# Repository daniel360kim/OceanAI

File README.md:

<!-- Project Logo -->
<div align="center">

  <h1 align="center">OceanAI</h1>
  
  <p align="center">
    A robotic and software orientated ocean development.
    <br />
    <a href="https://www.youtube.com/watch?v=8TJVxcPY-2g&t=32s&ab_channel=NMRocketry"><strong>See the video »</strong></a>
    <br />
    <br />
  </p>
</div>

<br>
  <h2>Table of Contents</h2>
  <ol>
    <li>
      <a href="#about-the-project">About The Project</a>
    </li>
    <li>
      <a href="#getting-started">Getting Started</a>
      <ul>
        <li><a href="#AUV Software">AUV Software</a></li>
        <li><a href="#Graphical User Interface">Graphical User Interface</a></li>
      </ul>
    </li>
    <li><a href="#license">License</a></li>
    <li><a href="#contact">Contact</a></li>
  </ol>

# About the Project
This project aims at creating an autonomous underwater vehicle (AUV) that utilizes cameras, sensors, a microcontroller, and GPS to categorize, identify, and map underwater trash. Detection of litter will be performed with a deep learning model - optimized to run on a microcontroller - allowing for cheap and power-efficient inference of underwater footage.

Main components of the project include:
* [AUV Control Board](https://github.com/daniel360kim/OceanAI/tree/master/PCBs)
* [AUV Software](https://github.com/daniel360kim/OceanAI/tree/master/software/sub_driver)
* [AUV CAD Model](https://github.com/daniel360kim/OceanAI/tree/master/CAD)
* [Deep Learning Model](https://github.com/daniel360kim/OceanAI/tree/master/software/detection_model)

# Getting Started
## AUV Software
[VSCode](https://code.visualstudio.com/) and
[PlatformIO](https://platformio.org/) are used to build and upload the software to the AUV.
1. Install VSCode and the PlatformIO extension.
2. Clone the repository.
```sh
git clone https://github.com/daniel360kim/OceanAI.git
```
3. Go to PlatformIO home and go to the 'Projects' tab.
4. Click 'Add Existing Project' and select the `software/sub_driver` folder.
5. Make sure you have the Teensy 4.1 core installed.
6. Connect the AUV through USB and click the 'Upload' button.
<br></br>

## Graphical User Interface

<br></br>
The GUI is built using [ElectricUI](https://electricui.com/). ElectricUI requires:
* [Node.js](https://nodejs.org/en/)
* [Yarn](https://yarnpkg.com/)

1. Install Node.js, [available from their website](https://nodejs.org/en/).
2. Install Yarn.
```sh
npm install -g yarn
```
3. Install ElectricUI, [available here](https://registry.eui.io/arc/latest/arc_latest_windows_amd64.msi)
4. Check everything installed and can be found in your PATH
```sh
arc info
```
5. Clone the repository if you haven't already.
```sh
git clone https://github.com/daniel360kim/OceanAI.git
```
6. Open the GUI project with ElectricUI. `software/auv_gui`
7. Run the GUI.
```sh
arc start
```

# License
Distributed under the MIT License. See `LICENSE` for more information.

# Contact
* Daniel Kim - nmrs.thrust@gmail.com - [YouTube](https://www.youtube.com/channel/UC0VazqJrUQiJGd_Tedn47zA) - Instagram: @us_rockets
* Project Link: https://github.com/daniel360kim/OceanAI

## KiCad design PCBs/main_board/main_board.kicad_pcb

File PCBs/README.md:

# PCBs
## Contains all the files for the printed circuit boards.

### main_board
* The PCB on the submarine that controls the submarine.
* This is the main board that controls navigation, outputs, loggins etc.

### transmitter_board
* This is an optional module that is floating in the water.
* It is connnected through a cable to the main board.
* It is above water so it can access GPS, RF, and other radio frequencies.

### sensor_board
* This board is at the front of the submarine. 
* It reads the underwater sensors and sends the data to the main board through I2C.
* It is not self powered - must have a clean 3.3V power supply.
* Programmed through SWD.

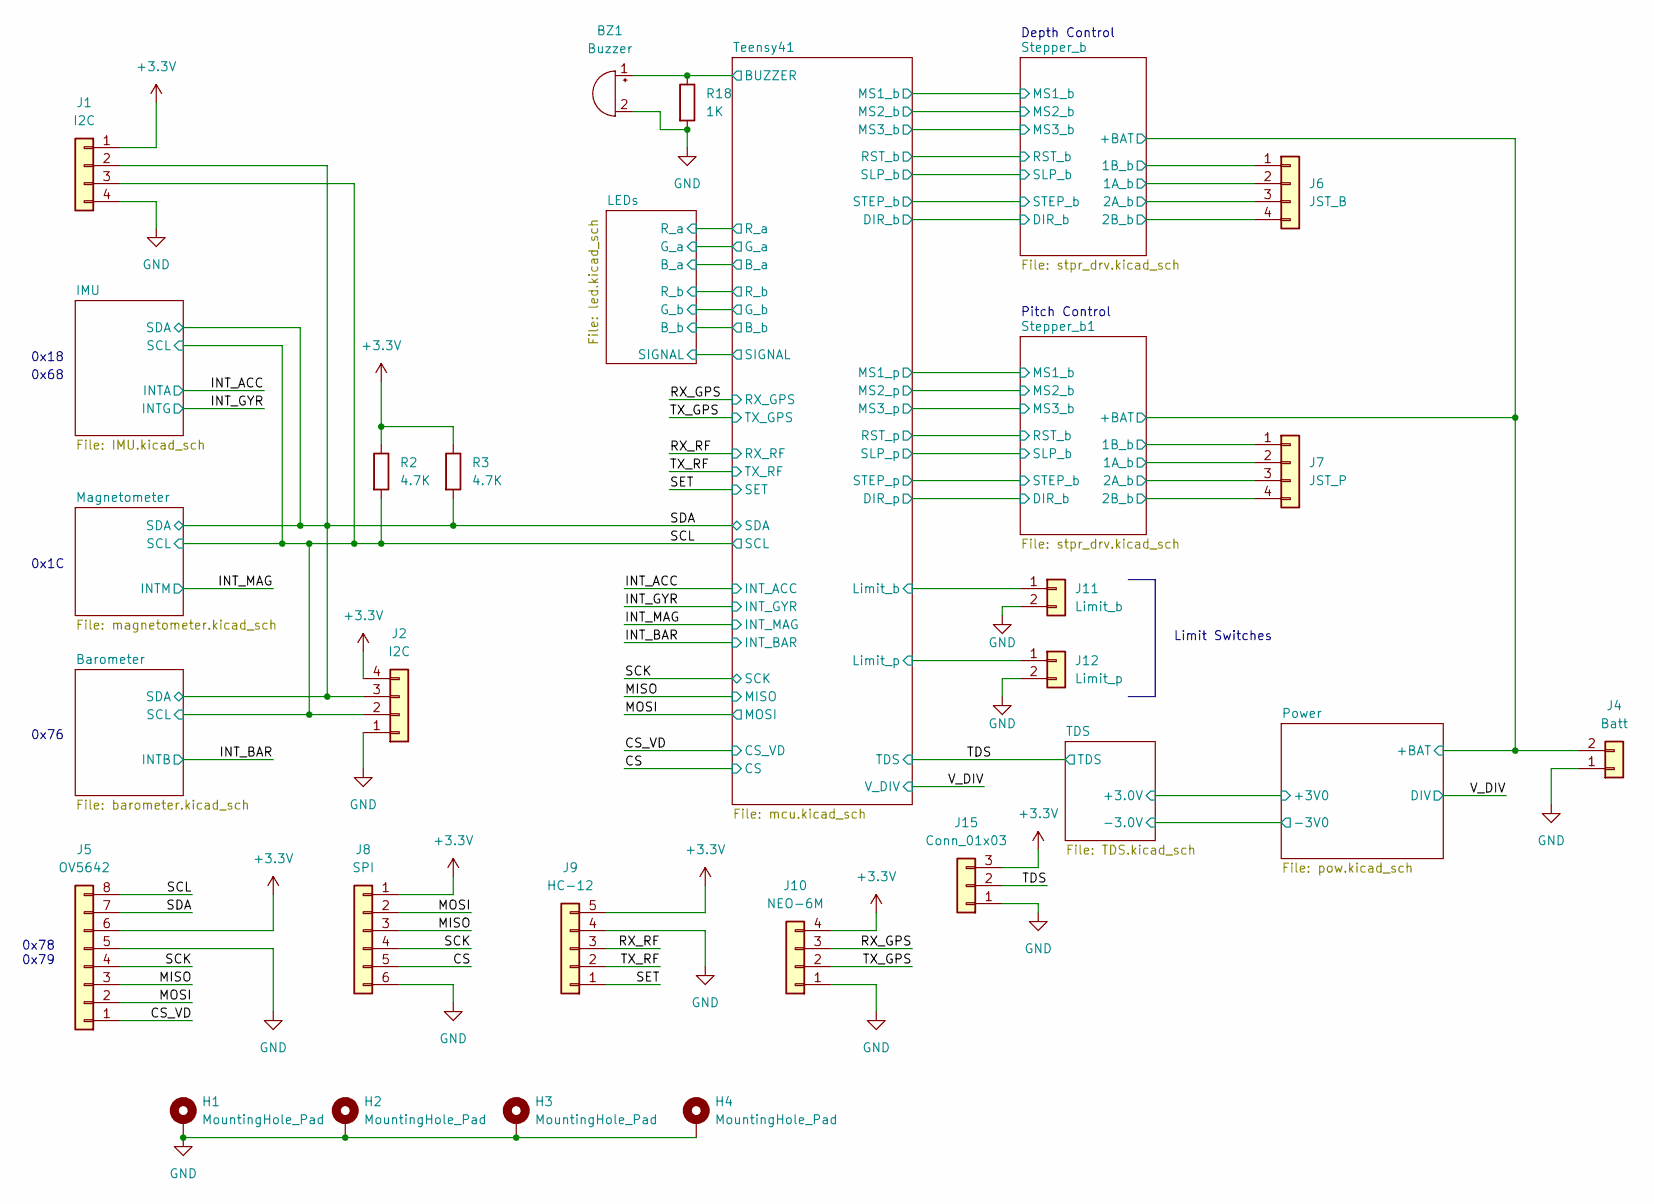
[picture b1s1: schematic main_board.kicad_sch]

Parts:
BZ1: Buzzer; Buzzer_Murata_PKMCS0909E
H1, H2, H3, H4: MountingHole_Pad; MountingHole_3mm_Pad
J1: I2C; JST_EH_B4B-EH-A_1x04_P2.50mm_Vertical
J2: I2C; PinHeader_1x04_P2.54mm_Vertical
J4: Batt; TerminalBlock_MetzConnect_Type101_RT01602HBWC_1x02_P5.08mm_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
J5: OV5642; JST_EH_B8B-EH-A_1x08_P2.50mm_Vertical
J6: JST_B; JST_EH_B4B-EH-A_1x04_P2.50mm_Vertical
J7: JST_P; JST_EH_B4B-EH-A_1x04_P2.50mm_Vertical
J8: SPI; PinHeader_1x06_P2.54mm_Vertical
J9: HC-12; JST_EH_B5B-EH-A_1x05_P2.50mm_Vertical
J10: NEO-6M; JST_EH_B4B-EH-A_1x04_P2.50mm_Vertical
J11: Limit_b; JST_EH_B2B-EH-A_1x02_P2.50mm_Vertical
J12: Limit_p; JST_EH_B2B-EH-A_1x02_P2.50mm_Vertical
J15: Conn_01x03; PinHeader_1x03_P2.54mm_Vertical
R2, R3: 4.7K; R_0603_1608Metric
R18: 1K; R_0603_1608Metric

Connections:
+3V3: J1.1, J2.4, J5.6, J8.1, J9.5, J10.4, J15.3, R2.1, R3.1; also elsewhere on the board
/CS: J8.5; also elsewhere on the board
/CS_VD: J5.1; also elsewhere on the board
/MISO: J5.3, J8.3; also elsewhere on the board
/MOSI: J5.2, J8.2; also elsewhere on the board
/RX_GPS: J10.3; also elsewhere on the board
/RX_RF: J9.3; also elsewhere on the board
/SCK: J5.4, J8.4; also elsewhere on the board
/SCL: J1.3, J2.2, J5.8, R2.2; also elsewhere on the board
/SDA: J1.2, J2.3, J5.7, R3.2; also elsewhere on the board
/SET: J9.1; also elsewhere on the board
/Stepper_b1/1A_b: J7.2; also elsewhere on the board
/Stepper_b1/1B_b: J7.1; also elsewhere on the board
/Stepper_b1/2A_b: J7.3; also elsewhere on the board
/Stepper_b1/2B_b: J7.4; also elsewhere on the board
/Stepper_b/1A_b: J6.2; also elsewhere on the board
/Stepper_b/1B_b: J6.1; also elsewhere on the board
/Stepper_b/2A_b: J6.3; also elsewhere on the board
/Stepper_b/2B_b: J6.4; also elsewhere on the board
/Stepper_b/VMM: J4.2; also elsewhere on the board
/TDS: J15.2; also elsewhere on the board
/TX_GPS: J10.2; also elsewhere on the board
/TX_RF: J9.2; also elsewhere on the board
/Teensy41/BUZZER: BZ1.1 (-), R18.1; also elsewhere on the board
/Teensy41/Limit_b: J11.1; also elsewhere on the board
/Teensy41/Limit_p: J12.1; also elsewhere on the board
GND: BZ1.2 (+), H1.1, H2.1, H3.1, H4.1, J1.4, J2.1, J4.1, J5.5, J8.6, J9.4, J10.1, J11.2, J12.2, J15.1, R18.2; also elsewhere on the board

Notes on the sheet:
Depth Control
0x1C
0x68
0x76
0x18
Pitch Control
Limit Switches
0x78 0x79

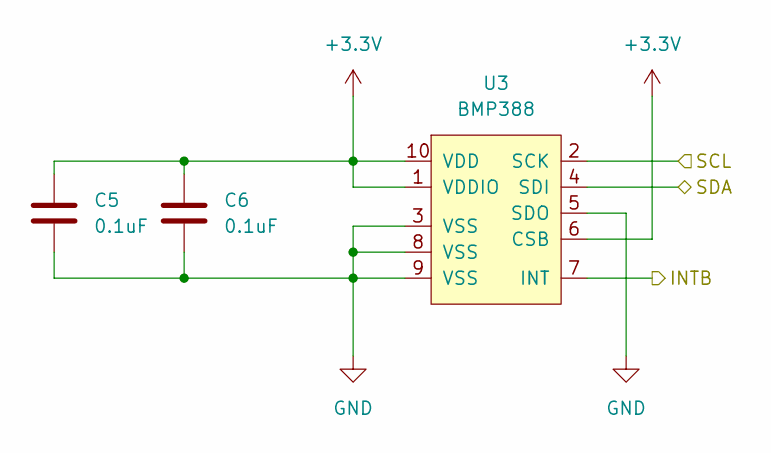
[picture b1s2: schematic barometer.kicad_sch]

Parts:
C5, C6: 0.1uF; C_0603_1608Metric
U3: BMP388; PQFN50P200X200X80-10N

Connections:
+3V3: C5.1, C6.1, U3.1 (VDDIO), U3.6 (CSB), U3.10 (VDD); also elsewhere on the board
/INT_BAR: U3.7 (INT); also elsewhere on the board
/SCL: U3.2 (SCK); also elsewhere on the board
/SDA: U3.4 (SDI); also elsewhere on the board
GND: C5.2, C6.2, U3.3 (VSS), U3.5 (SDO), U3.8 (VSS), U3.9 (VSS); also elsewhere on the board

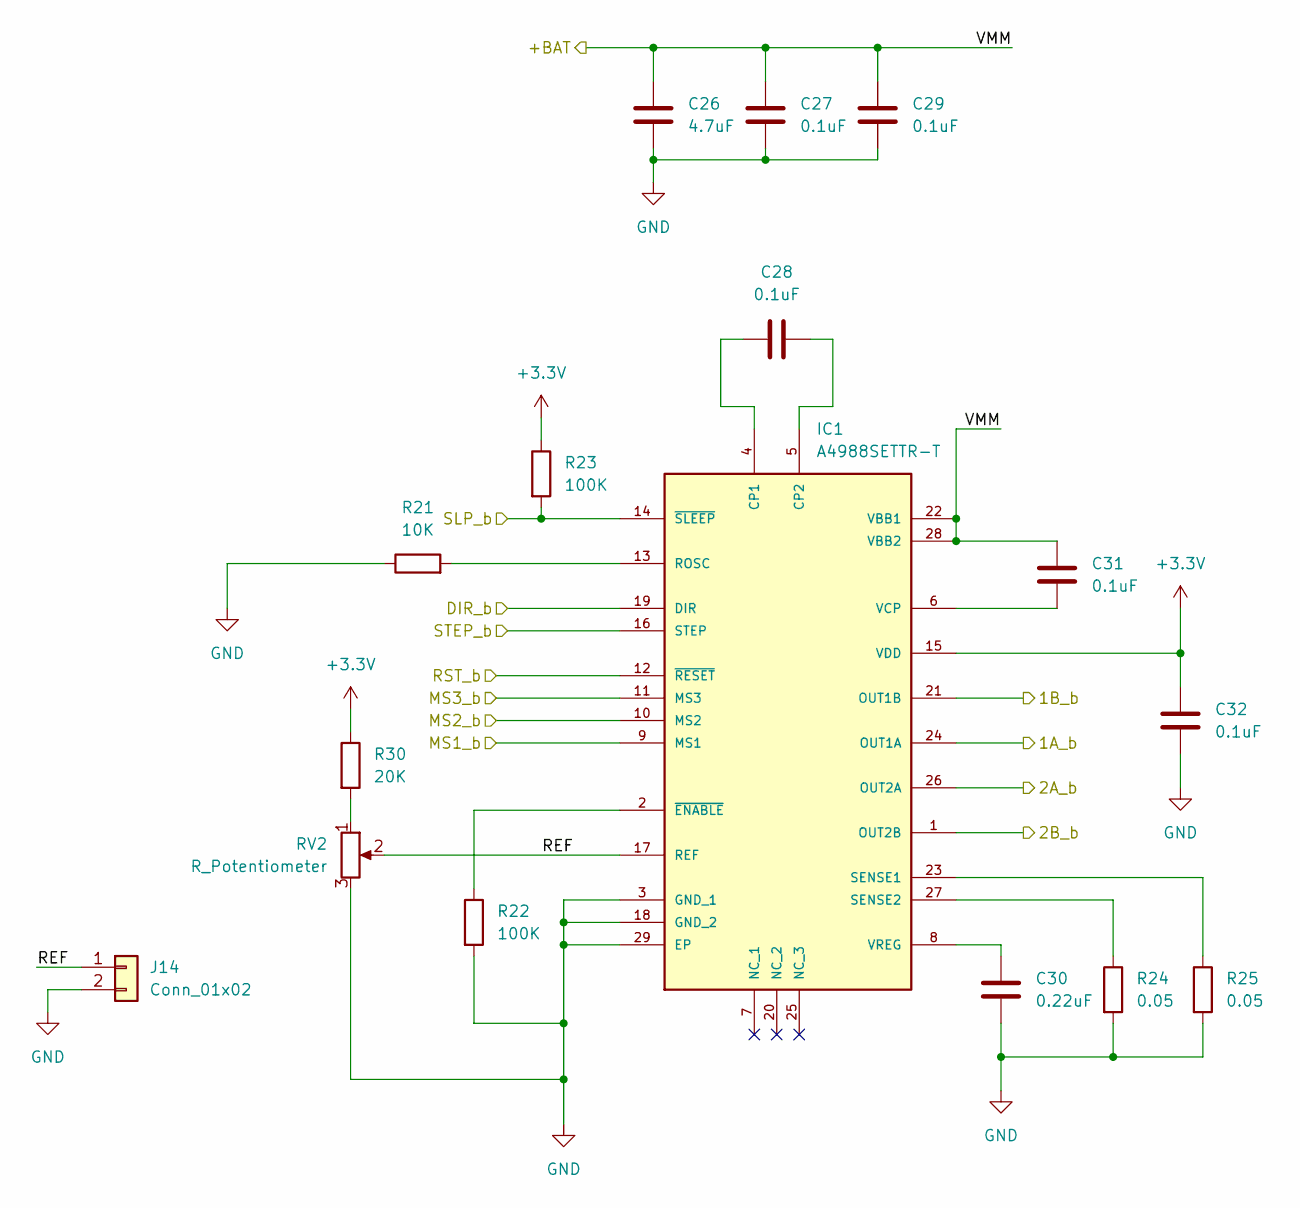
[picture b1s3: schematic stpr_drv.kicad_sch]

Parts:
C26: 4.7uF; C_0603_1608Metric
C27, C28, C29, C31, C32: 0.1uF; C_0603_1608Metric
C30: 0.22uF; C_0603_1608Metric
IC1: A4988SETTR-T; QFN50P500X500X100-29N; MANUFACTURER_PART_NUMBER A4988SETTR-T
J14: Conn_01x02; PinHeader_1x02_P2.54mm_Vertical
R21: 10K; R_0603_1608Metric
R22, R23: 100K; R_0603_1608Metric
R24, R25: 0.05; R_0603_1608Metric
R30: 20K; R_0603_1608Metric
RV2: R_Potentiometer; TRIM_35WR10KLFTR

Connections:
+3V3: C32.1, IC1.15 (VDD), R23.1, R30.1; also elsewhere on the board
/Stepper_b/1A_b: IC1.24 (OUT1A); also elsewhere on the board
/Stepper_b/1B_b: IC1.21 (OUT1B); also elsewhere on the board
/Stepper_b/2A_b: IC1.26 (OUT2A); also elsewhere on the board
/Stepper_b/2B_b: IC1.1 (OUT2B); also elsewhere on the board
/Stepper_b/DIR_b: IC1.19 (DIR); also elsewhere on the board
/Stepper_b/MS1_b: IC1.9 (MS1); also elsewhere on the board
/Stepper_b/MS2_b: IC1.10 (MS2); also elsewhere on the board
/Stepper_b/MS3_b: IC1.11 (MS3); also elsewhere on the board
/Stepper_b/REF: IC1.17 (REF), J14.1, RV2.2
/Stepper_b/RST_b: IC1.12 (~RESET); also elsewhere on the board
/Stepper_b/SLP_b: IC1.14 (~SLEEP), R23.2; also elsewhere on the board
/Stepper_b/STEP_b: IC1.16 (STEP); also elsewhere on the board
/Stepper_b/VMM: C26.1, C27.1, C29.1, C31.1, IC1.22 (VBB1), IC1.28 (VBB2); also elsewhere on the board
GND: C26.2, C27.2, C29.2, C30.2, C32.2, IC1.3 (GND_1), IC1.18 (GND_2), IC1.29 (EP), J14.2, R21.1, R22.2, R24.2, R25.2, RV2.3; also elsewhere on the board
unnamed: C28.1, IC1.4 (CP1)
unnamed: C28.2, IC1.5 (CP2)
unnamed: C30.1, IC1.8 (VREG)
unnamed: C31.2, IC1.6 (VCP)
unnamed: IC1.2 (~ENABLE), R22.1
unnamed: IC1.13 (ROSC), R21.2
unnamed: IC1.23 (SENSE1), R25.1
unnamed: IC1.27 (SENSE2), R24.1
unnamed: R30.2, RV2.1

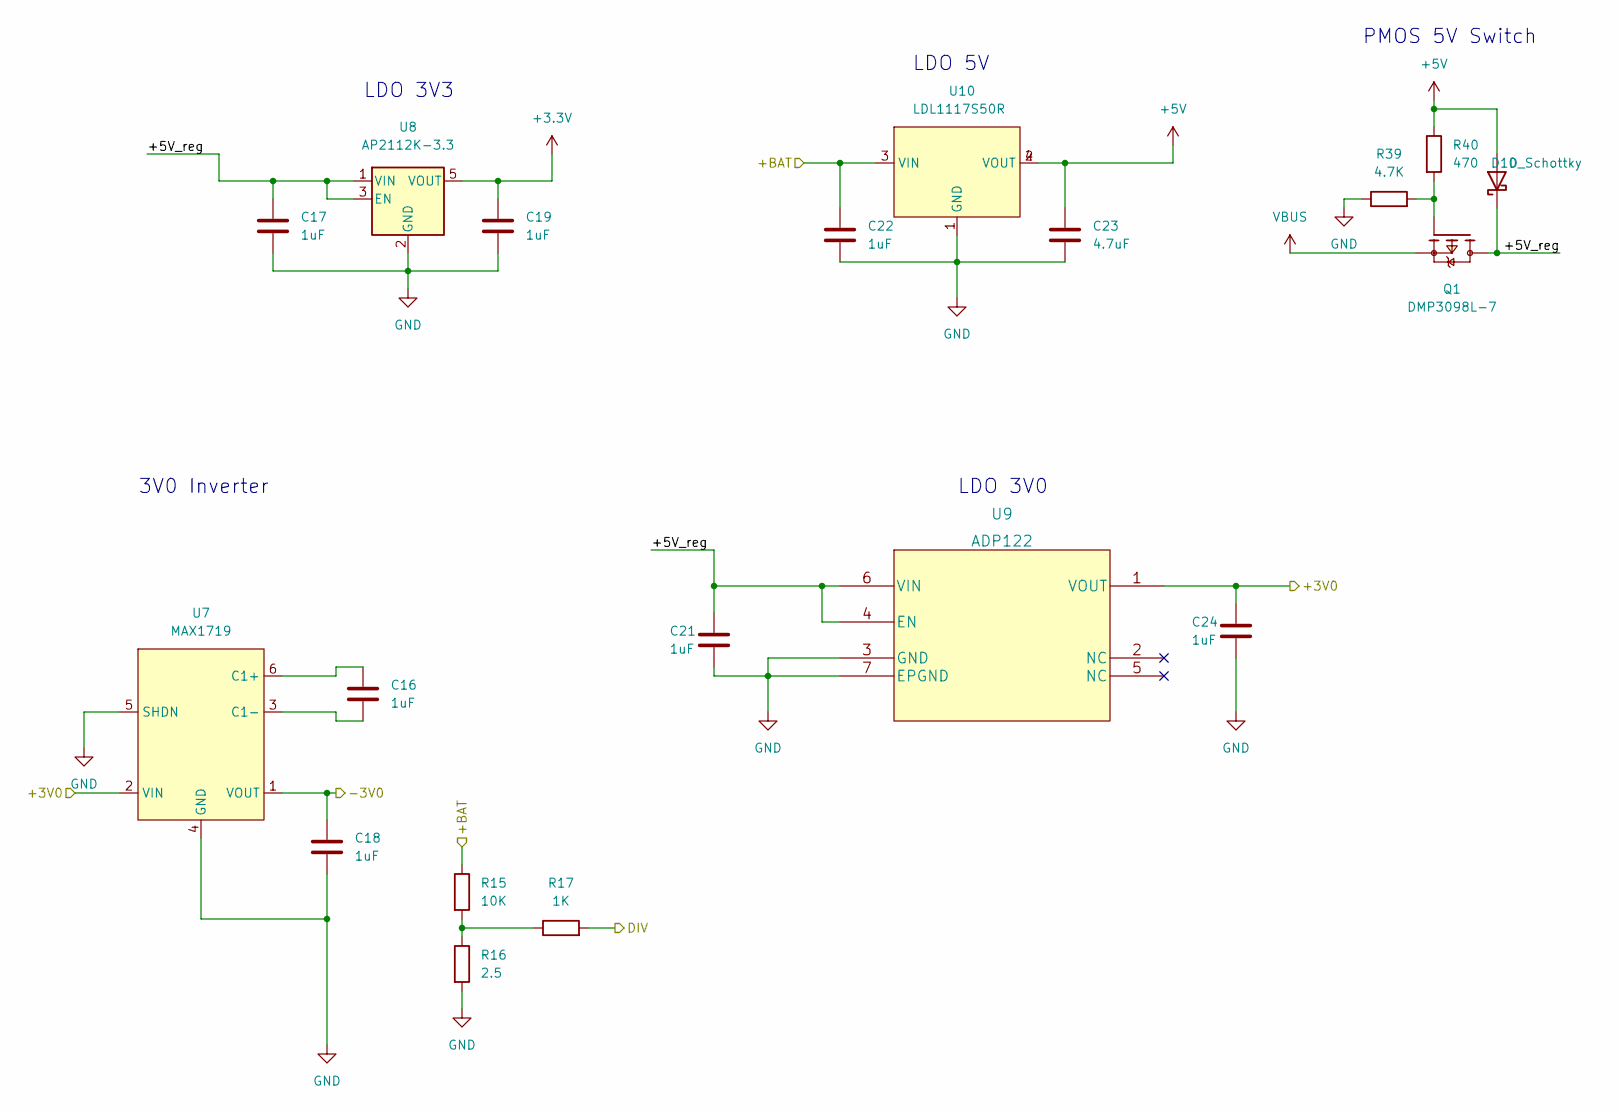
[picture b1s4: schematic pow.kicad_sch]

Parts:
C16, C17, C18, C19, C21, C22, C24: 1uF; C_0603_1608Metric
C23: 4.7uF; C_0603_1608Metric
D10: D_Schottky; DIOM4427X270N
Q1: DMP3098L-7; SOT91P240X110-3N; PARTREV 8 - 2
R15: 10K; R_0603_1608Metric
R16: 2.5; R_0603_1608Metric
R17: 1K; R_0603_1608Metric
R39: 4.7K; R_0603_1608Metric
R40: 470; R_0603_1608Metric
U7: MAX1719; SOT95P280X145-6N
U8: AP2112K-3.3; SOT95P285X140-5N
U9: ADP122; SON65P200X200X65-7N
U10: LDL1117S50R; SOT230P700X180-4N

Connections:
+3V3: C19.1, U8.5 (VOUT); also elsewhere on the board
+5V: C23.1, D10.A, R40.1, U10.2 (VOUT), U10.4 (VOUT); also elsewhere on the board
/Power/+3V0: C24.1, U7.2 (VIN), U9.1 (VOUT); also elsewhere on the board
/Power/+5V_reg: C17.1, C21.1, D10.C (K), Q1.3, U8.1 (VIN), U8.3 (EN), U9.4 (EN), U9.6 (VIN)
/Stepper_b/VMM: C22.1, R15.1, U10.3 (VIN); also elsewhere on the board
/TDS/RST: C18.1, U7.1 (VOUT); also elsewhere on the board
/V_DIV: R17.2; also elsewhere on the board
GND: C17.2, C18.2, C19.2, C21.2, C22.2, C23.2, C24.2, R16.2, R39.1, U7.4 (GND), U7.5 (SHDN), U8.2 (GND), U9.3 (GND), U9.7 (EPGND), U10.1 (GND); also elsewhere on the board
unnamed: C16.1, U7.6 (C1+)
unnamed: C16.2, U7.3 (C1-)
unnamed: Q1.1, R39.2, R40.2
unnamed: R15.2, R16.1, R17.1
VBUS: Q1.2; also elsewhere on the board

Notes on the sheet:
PMOS 5V Switch
LDO 5V
3V0 Inverter
LDO 3V3
LDO 3V0

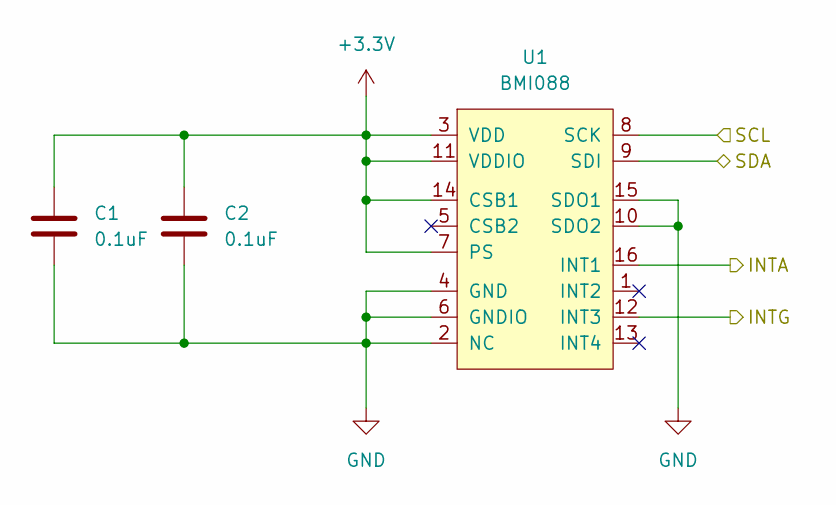
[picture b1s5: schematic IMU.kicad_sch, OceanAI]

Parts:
C1, C2: 0.1uF; C_0603_1608Metric
U1: BMI088; PQFN50P450X300X100-16N

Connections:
+3V3: C1.1, C2.1, U1.3 (VDD), U1.7 (PS), U1.11 (VDDIO), U1.14 (CSB1); also elsewhere on the board
/INT_ACC: U1.16 (INT1); also elsewhere on the board
/INT_GYR: U1.12 (INT3); also elsewhere on the board
/SCL: U1.8 (SCK); also elsewhere on the board
/SDA: U1.9 (SDI); also elsewhere on the board
GND: C1.2, C2.2, U1.2 (NC), U1.4 (GND), U1.6 (GNDIO), U1.10 (SDO2), U1.15 (SDO1); also elsewhere on the board

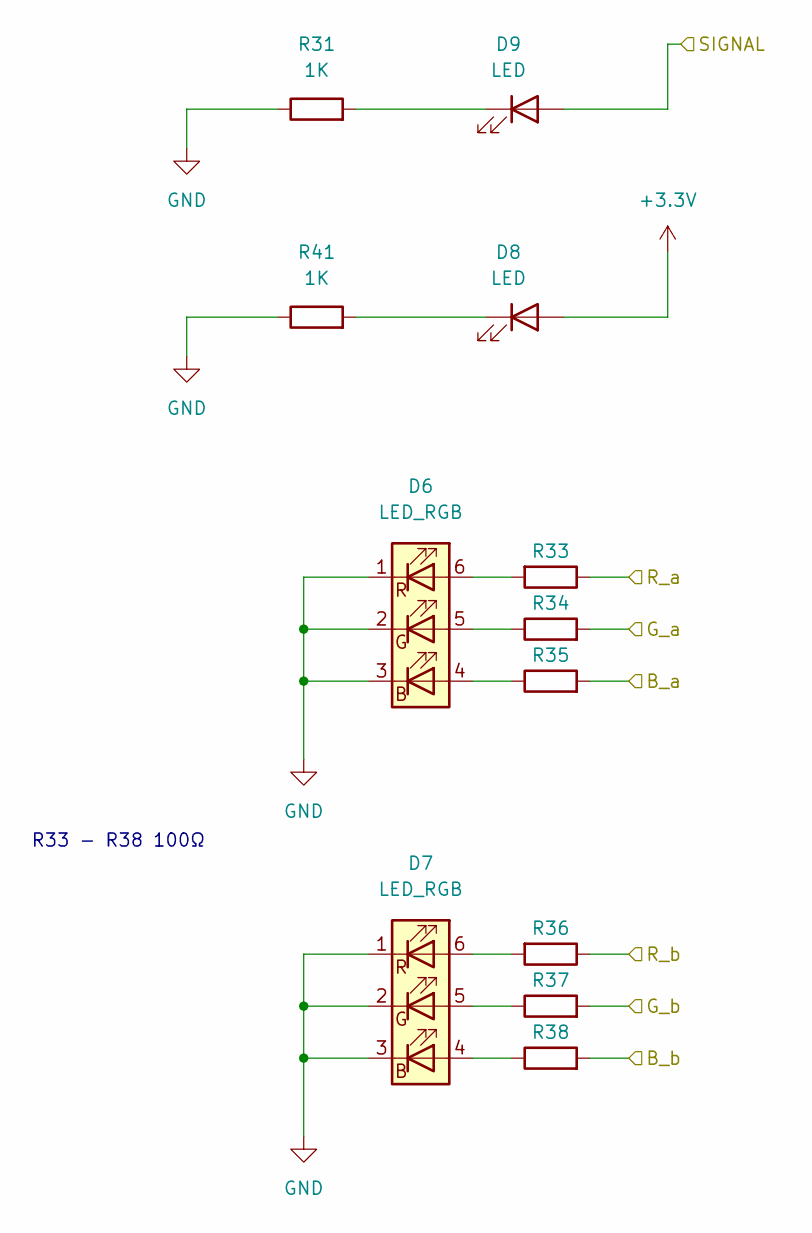
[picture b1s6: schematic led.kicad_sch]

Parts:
D6, D7: LED_RGB; LED_RGB_5050-6
D8, D9: LED; LED_0603_1608Metric
R31, R41: 1K; R_0603_1608Metric
R33, R35, R36, R38: R; R_0603_1608Metric
R34, R37: R_0603_1608Metric

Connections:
+3V3: D8.2 (A); also elsewhere on the board
/LEDs/B_a: R35.2; also elsewhere on the board
/LEDs/B_b: R38.2; also elsewhere on the board
/LEDs/G_a: R34.2; also elsewhere on the board
/LEDs/G_b: R37.2; also elsewhere on the board
/LEDs/R_a: R33.1; also elsewhere on the board
/LEDs/R_b: R36.1; also elsewhere on the board
/LEDs/SIGNAL: D9.2 (A); also elsewhere on the board
GND: D6.1 (RK), D6.2 (GK), D6.3 (BK), D7.1 (RK), D7.2 (GK), D7.3 (BK), R31.1, R41.1; also elsewhere on the board
unnamed: D6.4 (BA), R35.1
unnamed: D6.5 (GA), R34.1
unnamed: D6.6 (RA), R33.2
unnamed: D7.4 (BA), R38.1
unnamed: D7.5 (GA), R37.1
unnamed: D7.6 (RA), R36.2
unnamed: D8.1 (K), R41.2
unnamed: D9.1 (K), R31.2

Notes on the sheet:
R33 - R38 100Ω

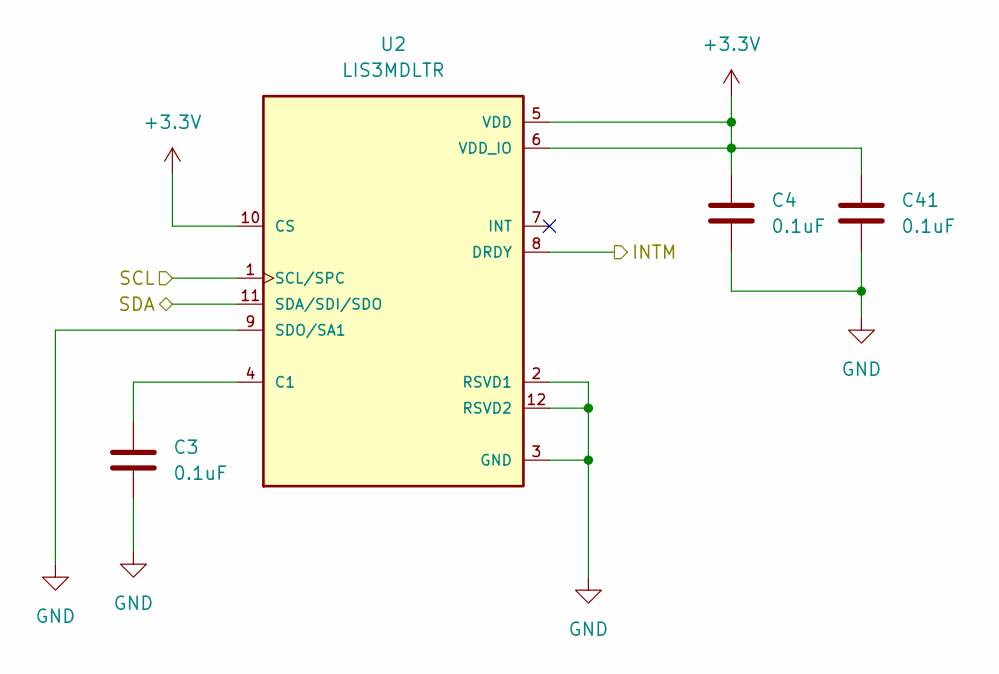
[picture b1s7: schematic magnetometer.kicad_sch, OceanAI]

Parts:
C3, C4, C41: 0.1uF; C_0603_1608Metric
U2: LIS3MDLTR; XDCR_LIS3MDLTR; PARTREV 6

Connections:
+3V3: C4.1, C41.1, U2.5 (VDD), U2.6 (VDD_IO), U2.10 (CS); also elsewhere on the board
/INT_MAG: U2.8 (DRDY); also elsewhere on the board
/SCL: U2.1 (SCL/SPC); also elsewhere on the board
/SDA: U2.11 (SDA/SDI/SDO); also elsewhere on the board
GND: C3.2, C4.2, C41.2, U2.2 (RSVD1), U2.3 (GND), U2.9 (SDO/SA1), U2.12 (RSVD2); also elsewhere on the board
unnamed: C3.1, U2.4 (C1)

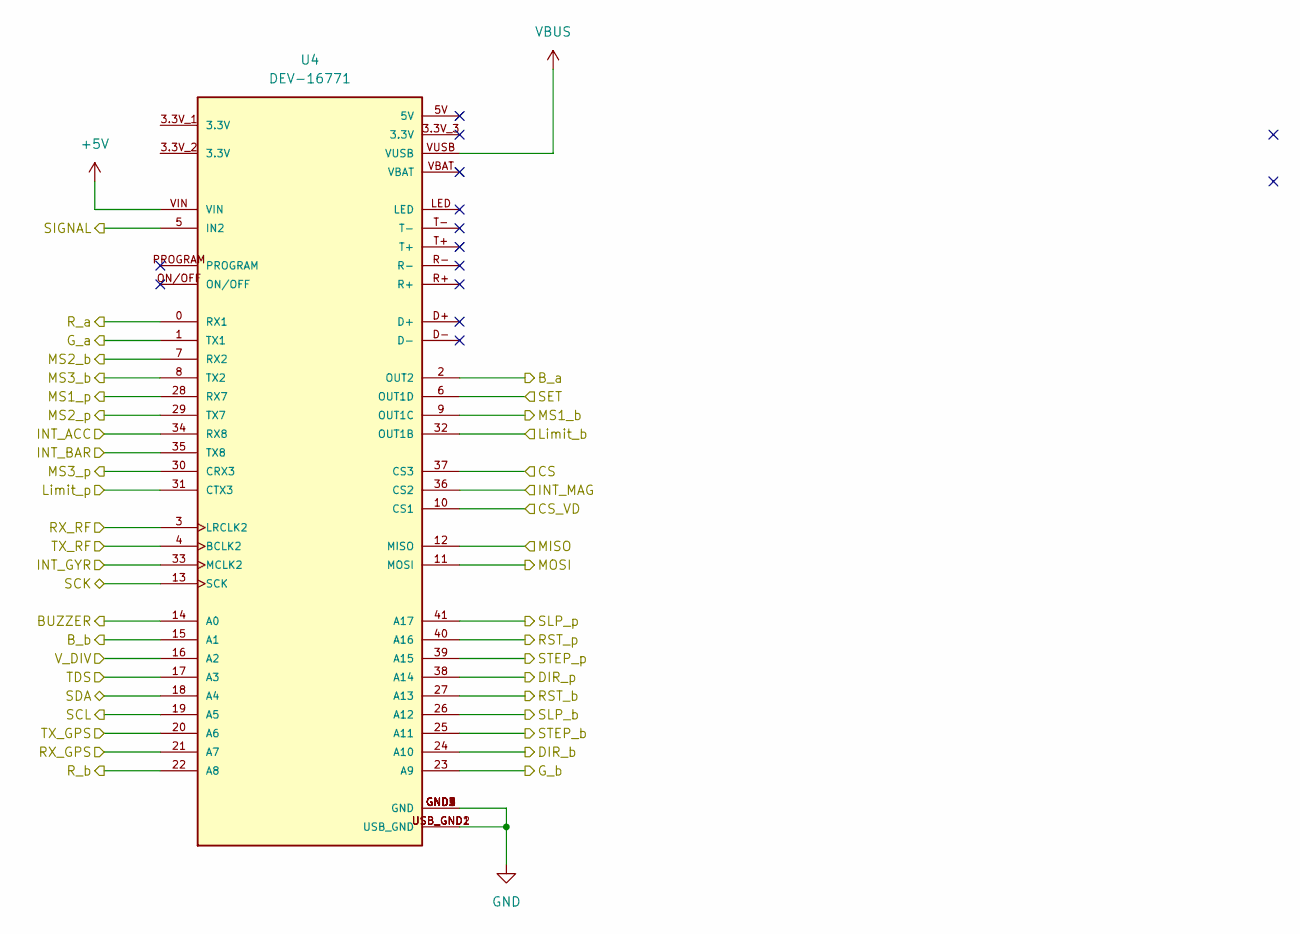
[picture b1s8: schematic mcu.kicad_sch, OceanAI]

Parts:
U4: DEV-16771; MODULE_DEV-16771; PARTREV 4.1

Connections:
+5V: U4.VIN; also elsewhere on the board
/CS: U4.37 (CS3); also elsewhere on the board
/CS_VD: U4.10 (CS1); also elsewhere on the board
/INT_ACC: U4.34 (RX8); also elsewhere on the board
/INT_BAR: U4.35 (TX8); also elsewhere on the board
/INT_GYR: U4.33 (MCLK2); also elsewhere on the board
/INT_MAG: U4.36 (CS2); also elsewhere on the board
/LEDs/B_a: U4.2 (OUT2); also elsewhere on the board
/LEDs/B_b: U4.15 (A1); also elsewhere on the board
/LEDs/G_a: U4.1 (TX1); also elsewhere on the board
/LEDs/G_b: U4.23 (A9); also elsewhere on the board
/LEDs/R_a: U4.0 (RX1); also elsewhere on the board
/LEDs/R_b: U4.22 (A8); also elsewhere on the board
/LEDs/SIGNAL: U4.5 (IN2); also elsewhere on the board
/MISO: U4.12 (MISO); also elsewhere on the board
/MOSI: U4.11 (MOSI); also elsewhere on the board
/RX_GPS: U4.21 (A7); also elsewhere on the board
/RX_RF: U4.3 (LRCLK2); also elsewhere on the board
/SCK: U4.13 (SCK); also elsewhere on the board
/SCL: U4.19 (A5); also elsewhere on the board
/SDA: U4.18 (A4); also elsewhere on the board
/SET: U4.6 (OUT1D); also elsewhere on the board
/Stepper_b1/DIR_b: U4.38 (A14); also elsewhere on the board
/Stepper_b1/MS1_b: U4.28 (RX7); also elsewhere on the board
/Stepper_b1/MS2_b: U4.29 (TX7); also elsewhere on the board
/Stepper_b1/MS3_b: U4.30 (CRX3); also elsewhere on the board
/Stepper_b1/RST_b: U4.40 (A16); also elsewhere on the board
/Stepper_b1/SLP_b: U4.41 (A17); also elsewhere on the board
/Stepper_b1/STEP_b: U4.39 (A15); also elsewhere on the board
/Stepper_b/DIR_b: U4.24 (A10); also elsewhere on the board
/Stepper_b/MS1_b: U4.9 (OUT1C); also elsewhere on the board
/Stepper_b/MS2_b: U4.7 (RX2); also elsewhere on the board
/Stepper_b/MS3_b: U4.8 (TX2); also elsewhere on the board
/Stepper_b/RST_b: U4.27 (A13); also elsewhere on the board
/Stepper_b/SLP_b: U4.26 (A12); also elsewhere on the board
/Stepper_b/STEP_b: U4.25 (A11); also elsewhere on the board
/TDS: U4.17 (A3); also elsewhere on the board
/TX_GPS: U4.20 (A6); also elsewhere on the board
/TX_RF: U4.4 (BCLK2); also elsewhere on the board
/Teensy41/BUZZER: U4.14 (A0); also elsewhere on the board
/Teensy41/Limit_b: U4.32 (OUT1B); also elsewhere on the board
/Teensy41/Limit_p: U4.31 (CTX3); also elsewhere on the board
/V_DIV: U4.16 (A2); also elsewhere on the board
GND: U4.GND1 (GND), U4.GND2 (GND), U4.GND3 (GND), U4.GND4 (GND), U4.GND5 (GND), U4.USB_GND1 (USB_GND), U4.USB_GND2 (USB_GND); also elsewhere on the board
VBUS: U4.VUSB; also elsewhere on the board

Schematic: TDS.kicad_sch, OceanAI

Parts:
C7: 1nF; C_0603_1608Metric
C8, C9, C14, C15: 0.1uF; C_0603_1608Metric
C10, C13: 1uF; C_0603_1608Metric
C11, C12: 4.7uF; C_0603_1608Metric
D1, D2, D3, D4, D5: 1N4148WS; D_SOD-323
J3: PROBE; TerminalBlock_MetzConnect_Type101_RT01602HBWC_1x02_P5.08mm_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
R1: 1M; R_0603_1608Metric
R4: 5.6K; R_0603_1608Metric
R5: 6.8K; R_0603_1608Metric
R6, R8: 100K; R_0603_1608Metric
R7, R9, R10, R11, R12, R13, R14: 10K; R_0603_1608Metric
U5: LM324A; SOIC127P600X175-14N
U6: CD4060BM; SOIC127P600X175-16N

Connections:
/Power/+3V0: C8.1, C11.1, C14.1, U5.4 (V+), U6.16 (VCC); also elsewhere on the board
/TDS: C13.1, D5.1 (K), R14.2; also elsewhere on the board
/TDS/RST: C9.1, C12.1, C15.1, U5.11 (V-), U6.8 (GND), U6.12 (RESET); also elsewhere on the board
GND: C8.2, C9.2, C10.2, C11.2, C12.2, C13.2, C14.2, C15.2, D5.2 (A), R1.2, U5.3 (+), U5.5 (+), U5.10 (+); also elsewhere on the board
unnamed: C7.1, R7.1, R8.1
unnamed: C7.2, U6.9 (EN1)
unnamed 62: C10.1, R13.2, R14.1; also elsewhere on the board
unnamed: D1.1 (K), D3.2 (A), U5.7
unnamed: D1.2 (A), R9.2, R11.1, U5.6 (-)
unnamed: D2.1 (K), D4.2 (A), U5.14
unnamed: D2.2 (A), R12.1, U5.13 (-)
unnamed 77: D3.1 (K), D4.1 (K), R11.2, R12.2, R13.1; also elsewhere on the board
unnamed: J3.1, R1.1, R4.1, U5.9 (-)
unnamed: J3.2, R5.1, U5.1
unnamed: R5.2, R6.1, U5.2 (-)
unnamed: R6.2, U6.7 (Q4)
unnamed: R7.2, U6.10 (EN2)
unnamed: R8.2, U6.11 (EN3)
unnamed: R4.2, R9.1, R10.1, U5.8
unnamed: R10.2, U5.12 (+)

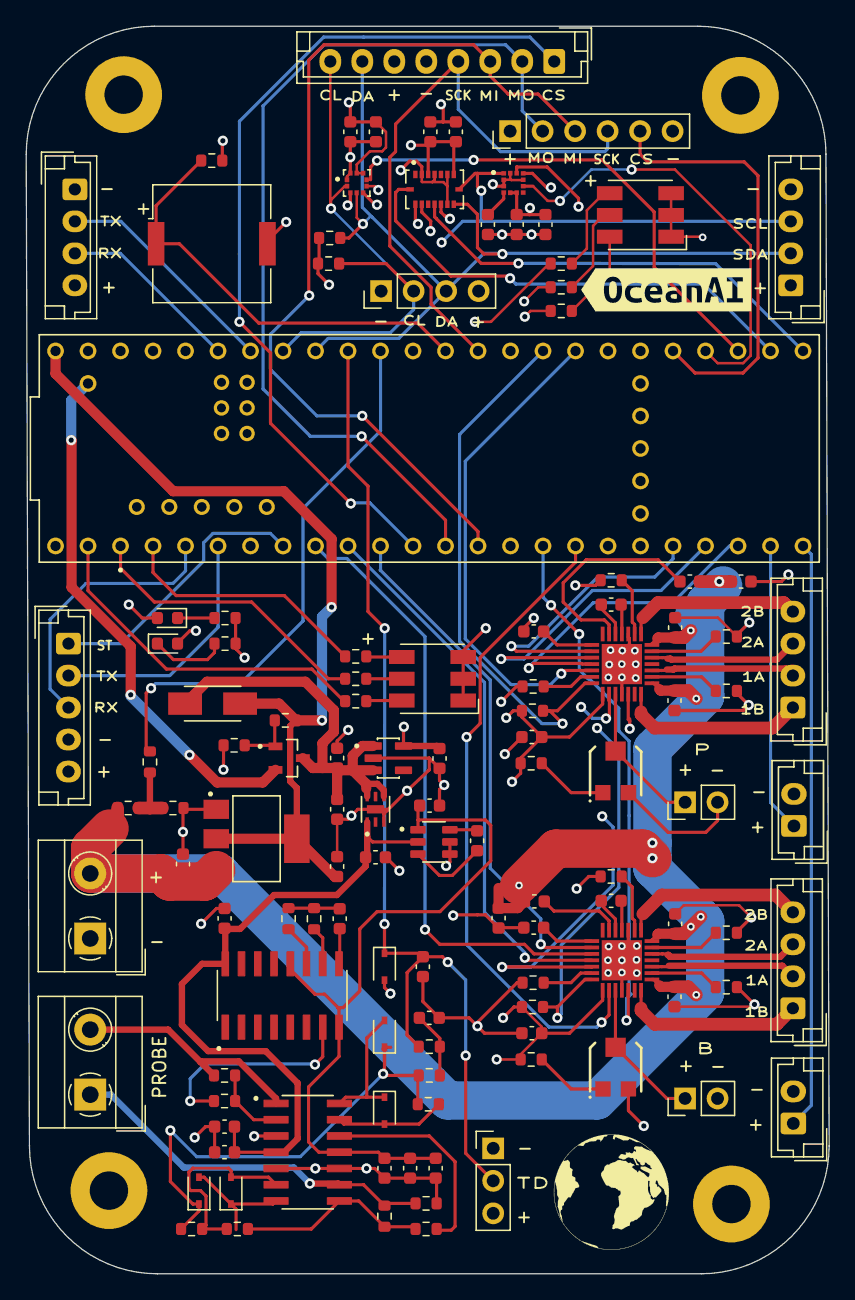
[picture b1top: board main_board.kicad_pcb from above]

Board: 4 copper layers, 62.8 x 97.5 mm, 124 parts (0 on the bottom side), 107 nets.

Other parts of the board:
C20: 4.7uF; C_0603_1608Metric
C25, C33, C34, C36, C37: 0.1uF; C_0603_1608Metric
C35: 0.22uF; C_0603_1608Metric
IC2: A4988SETTR-T; QFN50P500X500X100-29N
J13: Conn_01x02; PinHeader_1x02_P2.54mm_Vertical
R19: 20K; R_0603_1608Metric
R20: 10K; R_0603_1608Metric
R26, R27: 100K; R_0603_1608Metric
R28, R29: 0.05; R_0603_1608Metric
RV1: R_Potentiometer; TRIM_35WR10KLFTR
kibuzzard-1: G***; kibuzzard-629BEB6E
locked: 10K; R_0603_1608Metric

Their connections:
+3V3: C37.1, IC2.15 (VDD), R19.1, R27.1; also elsewhere on the board
/Stepper_b1/1A_b: IC2.24 (OUT1A); also elsewhere on the board
/Stepper_b1/1B_b: IC2.21 (OUT1B); also elsewhere on the board
/Stepper_b1/2A_b: IC2.26 (OUT2A); also elsewhere on the board
/Stepper_b1/2B_b: IC2.1 (OUT2B); also elsewhere on the board
/Stepper_b1/DIR_b: IC2.19 (DIR); also elsewhere on the board
/Stepper_b1/MS1_b: IC2.9 (MS1); also elsewhere on the board
/Stepper_b1/MS2_b: IC2.10 (MS2); also elsewhere on the board
/Stepper_b1/MS3_b: IC2.11 (MS3); also elsewhere on the board
/Stepper_b1/REF: IC2.17 (REF), J13.1, RV1.2
/Stepper_b1/RST_b: IC2.12 (~RESET); also elsewhere on the board
/Stepper_b1/SLP_b: IC2.14 (~SLEEP), R27.2; also elsewhere on the board
/Stepper_b1/STEP_b: IC2.16 (STEP); also elsewhere on the board
/Stepper_b/VMM: C20.1, C25.1, C34.1, C36.1, IC2.22 (VBB1), IC2.28 (VBB2); also elsewhere on the board
GND: C20.2, C25.2, C34.2, C35.2, C37.2, IC2.3 (GND_1), IC2.18 (GND_2), IC2.29 (EP), J13.2, R20.1, R26.2, R28.2, R29.2, RV1.3; also elsewhere on the board
unnamed 62: locked.2; also elsewhere on the board
unnamed: C33.1, IC2.4 (CP1)
unnamed: C33.2, IC2.5 (CP2)
unnamed: C35.1, IC2.8 (VREG)
unnamed: C36.2, IC2.6 (VCP)
unnamed 77: locked.1; also elsewhere on the board
unnamed: IC2.2 (~ENABLE), R26.1
unnamed: IC2.13 (ROSC), R20.2
unnamed: IC2.23 (SENSE1), R29.1
unnamed: IC2.27 (SENSE2), R28.1
unnamed: R19.2, RV1.1

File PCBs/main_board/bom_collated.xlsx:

Item | Item | Item | Value | LibPart | Footprint
1 | 1 | BZ1 | Buzzer | Device:Buzzer | Buzzer_Beeper:Buzzer_Murata_PKMCS0909E
2 | 21 | C1, C2, C3, C4, C5, C6, C8, C9, C14, C15, C25, C27, C28, C29, C31, C32, C33, C3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 | 0.1uF | Device:C | Capacitor_SMD:C_0603_1608Metric
3 | 1 | C7 | 1nF | Device:C | Capacitor_SMD:C_0603_1608Metric
4 | 7 | C10, C13, C17, C19, C21, C22, C24 | 1uF | Device:C | Capacitor_SMD:C_0603_1608Metric
5 | 5 | C11, C12, C20, C23, C26 | 4.7uF | Device:C | Capacitor_SMD:C_0603_1608Metric
6 | 2 | C16, C18 | 10uF | Device:C | Capacitor_SMD:C_0603_1608Metric
7 | 2 | C30, C35 | 0.22uF | Device:C | Capacitor_SMD:C_0603_1608Metric
8 | 5 | D1, D2, D3, D4, D5 | 1N4148WS | Diode:1N4148WS | Diode_SMD:D_SOD-323
9 | 2 | D6, D7 | LED_RGB | Device:LED_RGB | LED_SMD:LED_RGB_5050-6
10 | 2 | D8, D9 | LED | Device:LED | LED_SMD:LED_0603_1608Metric
11 | 4 | H1, H2, H3, H4 | MountingHole_Pad | Mechanical:MountingHole_Pad | MountingHole:MountingHole_3mm_Pad
12 | 2 | IC1, IC2 | A4988SETTR-T | A4988SETTR-T:A4988SETTR-T | A4988SETTR-T:QFN50P500X500X100-29N
13 | 1 | J1 | MS5803 | Connector_Generic:Conn_01x04 | Connector_JST:JST_EH_B4B-EH-A_1x04_P2.50mm_Vertical
14 | 1 | J2 | I2C | Connector_Generic:Conn_01x04 | Connector_PinHeader_2.54mm:PinHeader_1x04_P2.54mm_Vertical
15 | 1 | J3 | PROBE | Connector_Generic:Conn_01x02 | TerminalBlock_MetzConnect:TerminalBlock_MetzConnect_Type101_RT01602HBWC_1x02_P5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
16 | 1 | J4 | Batt | Connector_Generic:Conn_01x02 | TerminalBlock_MetzConnect:TerminalBlock_MetzConnect_Type101_RT01602HBWC_1x02_P5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
17 | 1 | J5 | OV5642 | Connector_Generic:Conn_01x08 | Connector_JST:JST_EH_B8B-EH-A_1x08_P2.50mm_Vertical
18 | 1 | J6 | JST_B | Connector_Generic:Conn_01x04 | Connector_JST:JST_EH_B4B-EH-A_1x04_P2.50mm_Vertical
19 | 1 | J7 | JST_P | Connector_Generic:Conn_01x04 | Connector_JST:JST_EH_B4B-EH-A_1x04_P2.50mm_Vertical
20 | 1 | J8 | I2C | Connector_Generic:Conn_01x06 | Connector_PinHeader_2.54mm:PinHeader_1x06_P2.54mm_Vertical
21 | 1 | J9 | HC-12 | Connector_Generic:Conn_01x05 | Connector_JST:JST_EH_B5B-EH-A_1x05_P2.50mm_Vertical
22 | 1 | J10 | NEO-6M | Connector_Generic:Conn_01x04 | Connector_JST:JST_EH_B4B-EH-A_1x04_P2.50mm_Vertical
23 | 1 | J11 | Limit_b | Connector_Generic:Conn_01x02 | Connector_JST:JST_EH_B2B-EH-A_1x02_P2.50mm_Vertical
24 | 1 | J12 | Limit_p | Connector_Generic:Conn_01x02 | Connector_JST:JST_EH_B2B-EH-A_1x02_P2.50mm_Vertical
25 | 2 | J13, J14 | Conn_01x02 | Connector_Generic:Conn_01x02 | Connector_PinHeader_2.54mm:PinHeader_1x02_P2.54mm_Vertical
26 | 1 | Q1 | DMP3098L-7 | DMP3098L-7:DMP3098L-7 | DMP3098L-7:SOT91P240X110-3N
27 | 1 | R1 | 1M | Device:R | Resistor_SMD:R_0603_1608Metric
28 | 3 | R2, R3, R39 | 4.7K | Device:R | Resistor_SMD:R_0603_1608Metric
29 | 1 | R4 | 5.6K | Device:R | Resistor_SMD:R_0603_1608Metric
30 | 1 | R5 | 6.8K | Device:R | Resistor_SMD:R_0603_1608Metric
31 | 6 | R6, R8, R22, R23, R26, R27 | 100K | Device:R | Resistor_SMD:R_0603_1608Metric
32 | 10 | R7, R9, R10, R11, R12, R13, R14, R15, R20, R21 | 10K | Device:R | Resistor_SMD:R_0603_1608Metric
33 | 1 | R16 | 2.5 | Device:R | Resistor_SMD:R_0603_1608Metric
34 | 4 | R17, R18, R31, R41 | 1K | Device:R | Resistor_SMD:R_0603_1608Metric
35 | 2 | R19, R30 | 20K | Device:R | Resistor_SMD:R_0603_1608Metric
36 | 4 | R24, R25, R28, R29 | 0.05 | Device:R | Resistor_SMD:R_0603_1608Metric
37 | 4 | R33, R35, R36, R38 | R | Device:R | Resistor_SMD:R_0603_1608Metric
38 | 2 | R34, R37 |  | Device:R | Resistor_SMD:R_0603_1608Metric
39 | 1 | R40 | 470 | Device:R | Resistor_SMD:R_0603_1608Metric
40 | 2 | RV1, RV2 | R_Potentiometer | Device:R_Potentiometer | 35WR10KLFTR:TRIM_35WR10KLFTR
41 | 1 | U1 | BMI088 | TBC_Sensors:BMI088 | BMI088:PQFN50P450X300X100-16N
42 | 1 | U2 | LIS3MDLTR | LIS3MDLTR:LIS3MDLTR | LIS3MDLTR:XDCR_LIS3MDLTR
43 | 1 | U3 | BMP388 | TBC_Sensors:BMP388 | BMP388:PQFN50P200X200X80-10N
44 | 1 | U4 | DEV-16771 | DEV-16771:DEV-16771 | DEV-16771:MODULE_DEV-16771
45 | 1 | U5 | LM324A | :LM324A_1 | LM324:SOIC127P600X175-14N
46 | 1 | U6 | CD4060BM | CD4060BM:CD4060BM | CD4060BM:SOIC127P600X175-16N
47 | 1 | U7 | ICL7662CBA-T | ICL7662CBA-T:ICL7662CBA-T | ICL7662CBA-T:SOIC127P600X175-8N
48 | 1 | U8 | AP2112K-3.3 | Regulator_Linear:AP2112K-3.3 | AP2112K-3:SOT95P285X140-5N
49 | 1 | U9 | ADP122 | ADP122:ADP122ACPZ-3.3-R7 | ADP122:SON65P200X200X65-7N
50 | 1 | U10 | LDL1117S50R | Regulator_Linear:LDL1117S50R | SOT230P700X180-4N:SOT230P700X180-4N

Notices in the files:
parts and their libraries:
COPYRIGHT: Copyright C 2016 Accelerated Designs. All rights reserved
